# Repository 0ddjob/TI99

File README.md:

# [PSU Replacement](/TI994A_PSU_Replacement)
A fork of a fork.  <br>
Created a version using KiCad 9, with rounded corners and more information to make the build more "idiot proof".<br>

Replaces the 99/4A's original dual-voltage 18VAC/7.5VAC power supply with a regulated 12VDC supply.  The board then generates the required ±5VDC voltages using a DC-DC buck converter (+5VDC) and switching regulator (-5VDC).  The +12VDC comes directly from the external power supply.<br>

## Main Parts
- DFRobot DFR0831 DC-DC Buck Converter (+5VDC supply)
- Recom R-78CK5.0-0.5 Switching Regulator (-5VDC supply)
- Vishay SUP53P06-20 MOSFET (protects against reverse polarity DC input)
- G-Switch SS-22G88-G090 DPDT switch (need to trim a little)

## Original Designs
- [Johnny Blanchard's original](https://codeberg.org/Jonn-reenthused/TI99-4A-dc-power-board)
- [dabone's fork](https://github.com/dabonetn/ti99psu-replacement)

## Status
- 2-Nov-2025: Designed, not yet fabbed & tested, need to double-check switch position

# [Joystick Adaptor](/JoystickAdaptor)
Wanted to design my own joystick adaptor, so I did.

# [Cassette Adaptor #1](/CassetteAdaptor)
Wanted to design a cassette adaptor as an alternative to using a cable because, why not?  I normally play WAV files from my computer using a cable - this design lets me simply plug the cable into.<br>

This design is vertical and plugs into the DE9 socket to provide a 3.5mm EAR and 3.5mm MIC socket for CS1.<br>

# [Cassette Adaptor #2](/CassetteAdaptor2)
This design is horizontal and plugs into the DE9 socket to provide a 3.5mm EAR and 3.5mm MIC socket for CS1.<br>

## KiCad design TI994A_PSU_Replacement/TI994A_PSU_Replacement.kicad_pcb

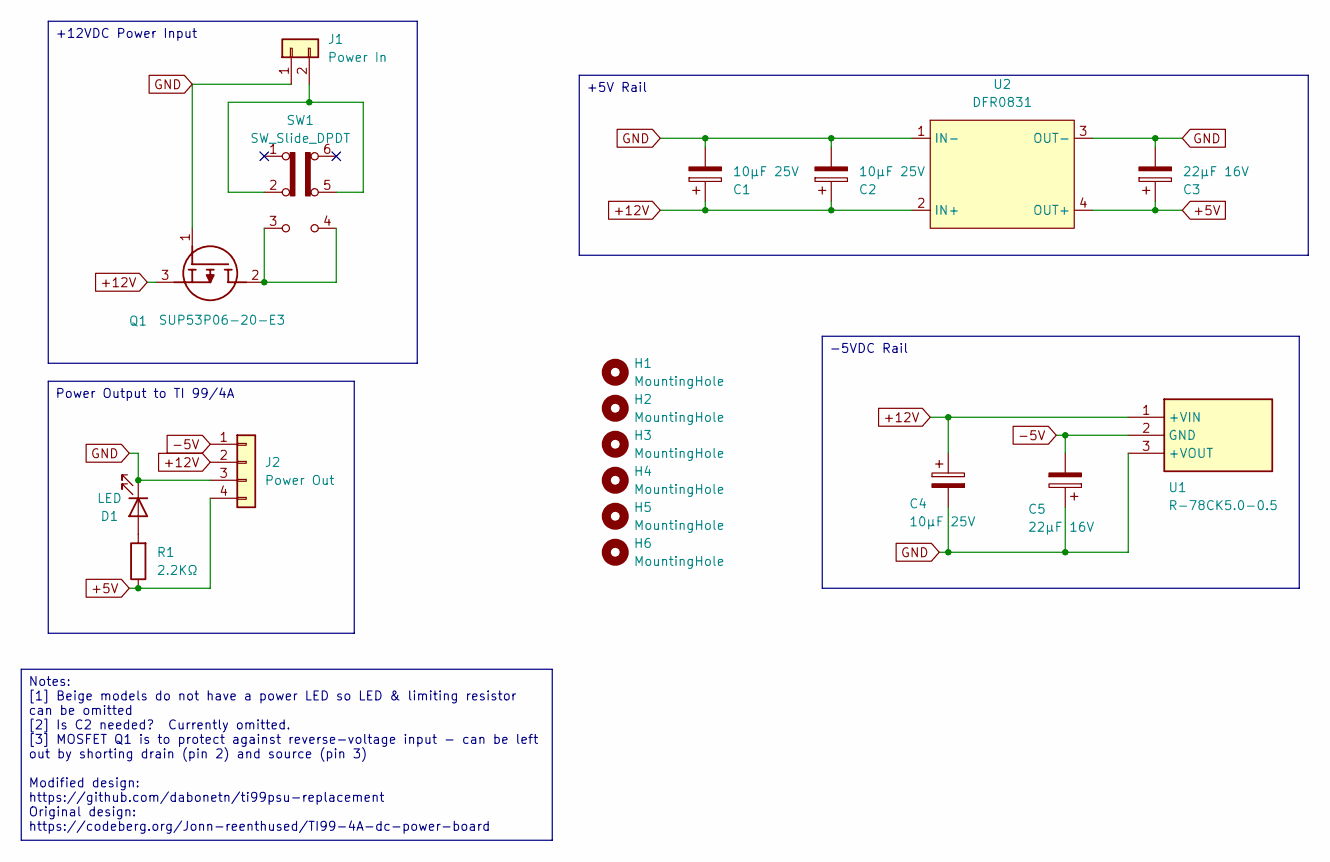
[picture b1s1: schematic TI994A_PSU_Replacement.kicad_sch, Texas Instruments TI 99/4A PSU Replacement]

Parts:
C1, C2, C4: 10µF 25V; C_Radial_D5.0mm_H5.0mm_P2.00mm
C3, C5: 22µF 16V; C_Radial_D5.0mm_H5.0mm_P2.00mm
D1: LED; LED_D5.0mm
H1, H2, H3, H4, H5: MountingHole; MountingHole_4mm
H6: MountingHole; MountingHole_6mm
J1: Power In; JST_VH_B2P-VH_1x02_P3.96mm_Vertical
J2: Power Out; JST_VH_B4P-VH_1x04_P3.96mm_Vertical
Q1: SUP53P06-20-E3; TO254P465X1028X1931-3P; Mouser Part Number 781-SUP53P06-20-E3
R1: 2.2KΩ; R_Axial_DIN0207_L6.3mm_D2.5mm_P7.62mm_Horizontal
SW1: SW_Slide_DPDT; SS-22G88-G090 DPDT
U1: R-78CK5.0-0.5; R78CK5005; Manufacturer_Part_Number R-78CK5.0-0.5
U2: DFR0831

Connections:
+5V: C3.1, J2.4, R1.1, U2.4 (OUT+)
+12V: C1.1, C2.1, C4.1, J2.2, Q1.3 (S), U1.1 (+VIN), U2.2 (IN+)
-5V: C5.2, J2.1, U1.2 (GND)
GND: C1.2, C2.2, C3.2, C4.2, C5.1, D1.1 (K), J1.1, J2.3, Q1.1 (G), U1.3 (+VOUT), U2.1 (IN-), U2.3 (OUT-)
unnamed: D1.2 (A), R1.2
unnamed: J1.2, SW1.2 (B), SW1.5 (B)
unnamed: Q1.2 (D), SW1.3 (C), SW1.4 (A)

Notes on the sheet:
+12VDC Power Input
-5VDC Rail
Power Output to TI 99/4A
Notes: [1] Beige models do not have a power LED so LED & limiting resistor can be omitted [2] Is C2 needed? Currently omitted. [3] MOSFET Q1 is to protect against reverse-voltage input - can be left out by shorting drain (pin 2) and source (pin 3) Modified design: https://github.com/dabonetn/ti99ps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
+5V Rail

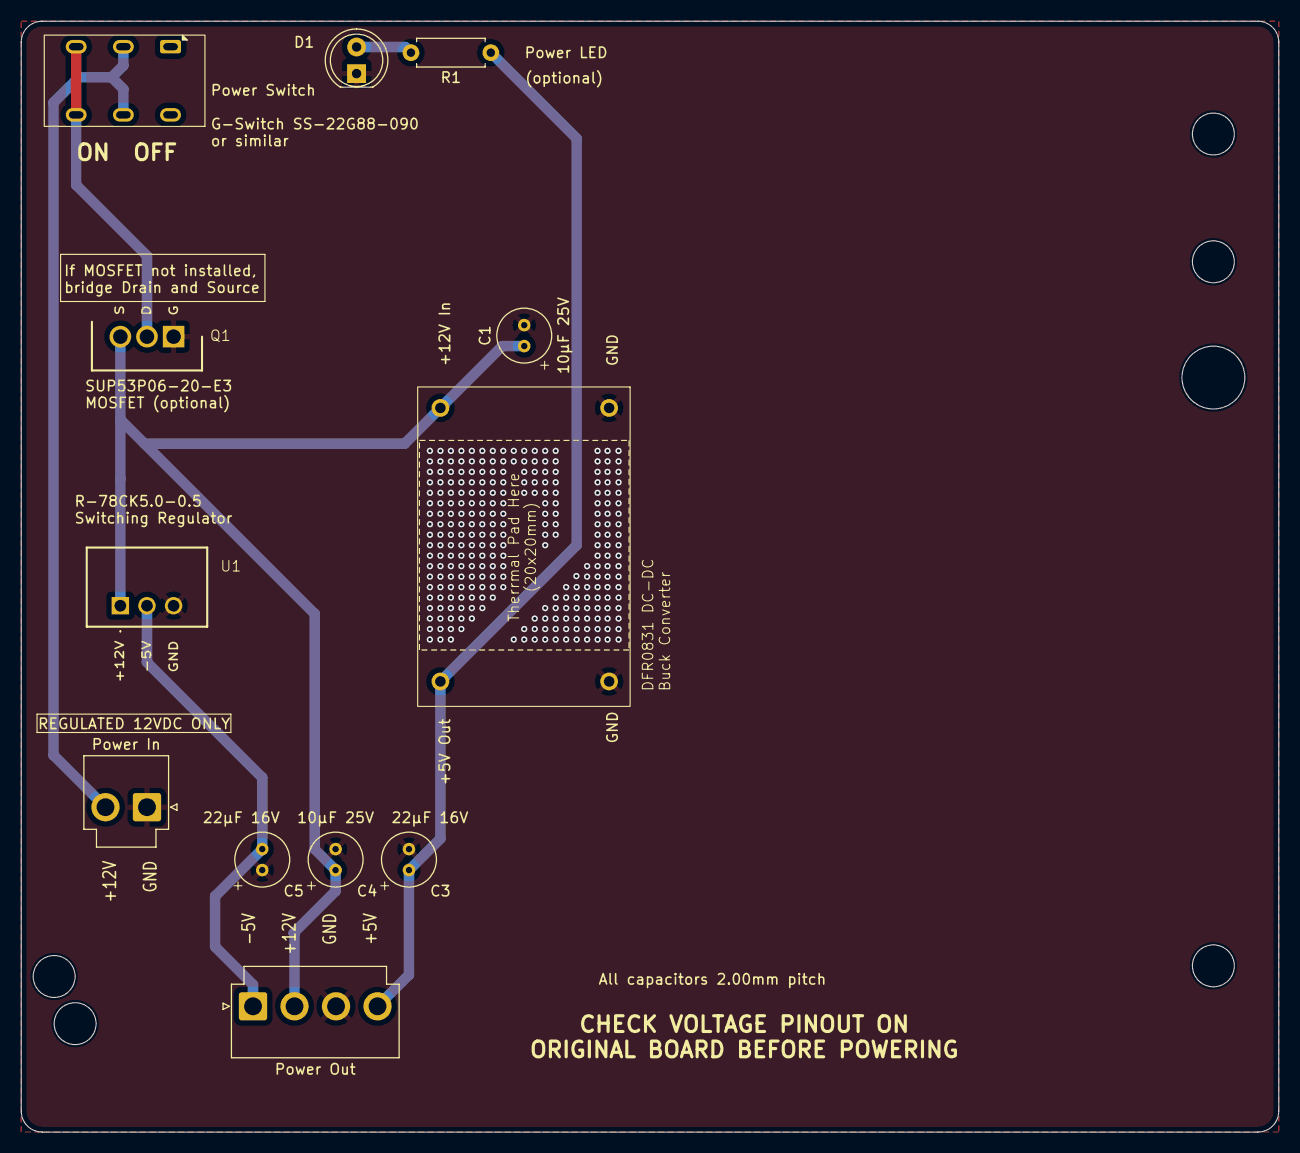
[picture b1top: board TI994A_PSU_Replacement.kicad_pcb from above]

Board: 2 copper layers, 120.0 x 106.0 mm, 18 parts (0 on the bottom side), 7 nets.

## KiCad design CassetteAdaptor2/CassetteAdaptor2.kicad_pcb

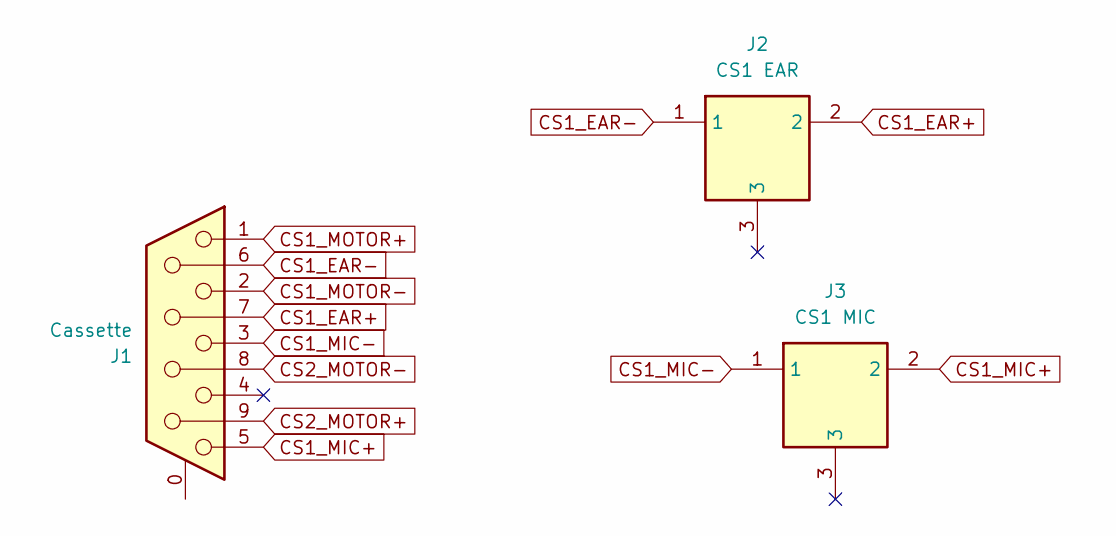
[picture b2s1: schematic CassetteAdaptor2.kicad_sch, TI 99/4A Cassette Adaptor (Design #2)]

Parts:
J1: Cassette; DSUB-9_Pins_EdgeMount_P2.77mm
J2: CS1 EAR; MJ3536N; Mouser Part Number 490-MJ-3536N
J3: CS1 MIC; MJ3536N; Mouser Part Number 490-MJ-3536N

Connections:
CS1_EAR+: J1.7, J2.2
CS1_EAR-: J1.6, J2.1
CS1_MIC+: J1.5, J3.2
CS1_MIC-: J1.3, J3.1
CS1_MOTOR+: J1.1
CS1_MOTOR-: J1.2
CS2_MOTOR+: J1.9
CS2_MOTOR-: J1.8

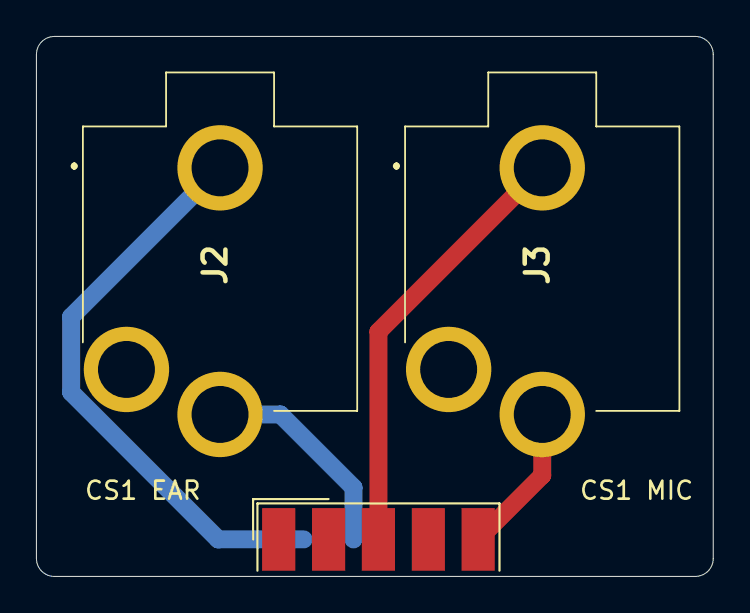
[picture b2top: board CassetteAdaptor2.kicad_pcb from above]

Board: 2 copper layers, 37.6 x 30.0 mm, 3 parts (0 on the bottom side), 4 nets.

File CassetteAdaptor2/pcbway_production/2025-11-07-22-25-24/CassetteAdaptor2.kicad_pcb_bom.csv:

Designator,Quantity,Value,Footprint,Package,MPN,DNP,Mount_Type,Description,Height,Mouser Part Number,Mouser Price/Stock,Manufacturer_Name
J1,1,Cassette,DSUB-9_Pins_EdgeMount_P2.77mm,,,,smt,"9-pin D-SUB connector, socket (female), Mounting Hole",,,,
J2,1,CS1 EAR,MJ3536N,,MJ-3536N,,tht,"3.5 mm, Mono, Right Angle, Through Hole, 2 Conductors, 1 Internal Switch, Audio Jack Connector",10,490-MJ-3536N,https://www.mouser.co.uk/ProductDetail/Same-Sky/MJ-3536N?qs=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,Same Sky
J3,1,CS1 MIC,MJ3536N,,MJ-3536N,,tht,"3.5 mm, Mono, Right Angle, Through Hole, 2 Conductors, 1 Internal Switch, Audio Jack Connector",10,490-MJ-3536N,https://www.mouser.co.uk/ProductDetail/Same-Sky/MJ-3536N?qs=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,Same Sky

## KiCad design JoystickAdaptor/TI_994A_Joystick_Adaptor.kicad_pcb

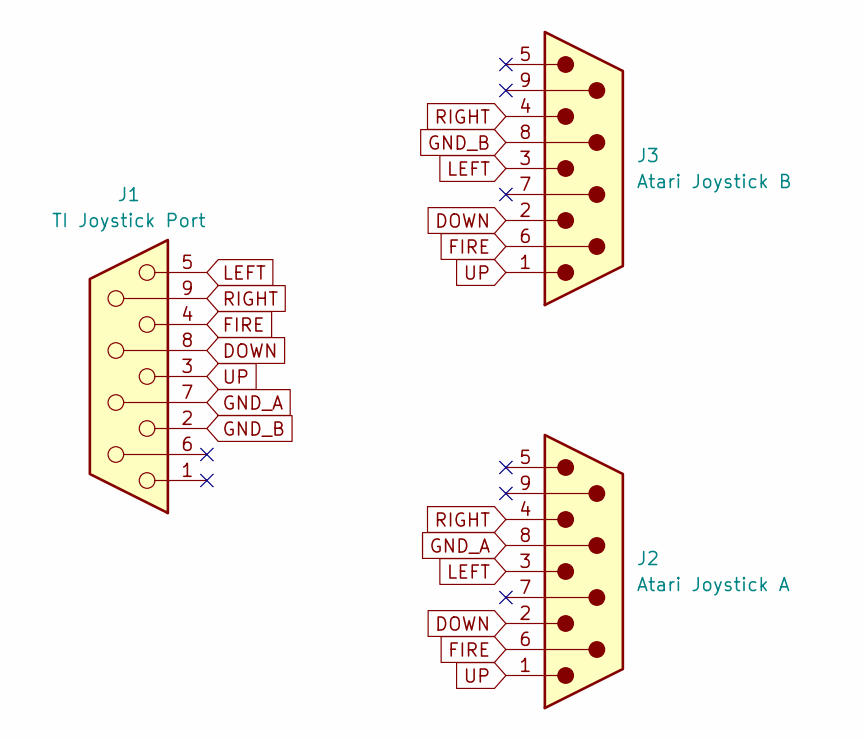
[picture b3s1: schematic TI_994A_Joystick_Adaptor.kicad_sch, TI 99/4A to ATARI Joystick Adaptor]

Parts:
J1: TI Joystick Port; DSUB-9_Socket_Vertical_P2.77x2.84mm
J2: Atari Joystick A; DSUB-9_Pins_Vertical_P2.77x2.84mm
J3: Atari Joystick B; DSUB-9_Pins_Vertical_P2.77x2.84mm

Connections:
DOWN: J1.8, J2.2, J3.2
FIRE: J1.4, J2.6, J3.6
GND_A: J1.7, J2.8
GND_B: J1.2, J3.8
LEFT: J1.5, J2.3, J3.3
RIGHT: J1.9, J2.4, J3.4
UP: J1.3, J2.1, J3.1

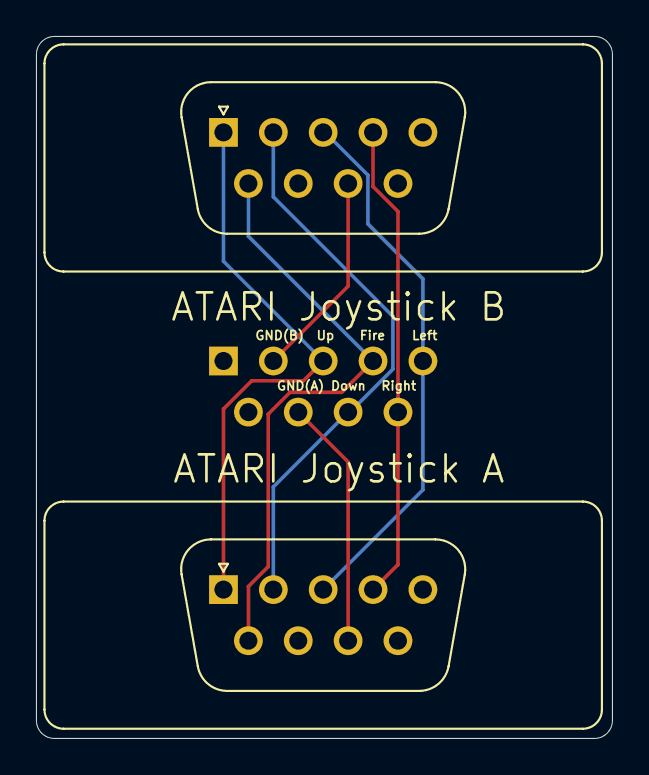
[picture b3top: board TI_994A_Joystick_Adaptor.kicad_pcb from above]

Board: 2 copper layers, 32.0 x 39.0 mm, 3 parts (1 on the bottom side), 7 nets.

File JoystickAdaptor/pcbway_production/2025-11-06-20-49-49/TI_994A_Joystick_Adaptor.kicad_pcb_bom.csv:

Designator,Quantity,Value,Footprint,Package,MPN,DNP,Mount_Type,Description
J1,1,TI Joystick Port,DSUB-9_Socket_Vertical_P2.77x2.84mm,,,,tht,"9-pin D-SUB connector, socket (female)"
J2,1,Atari Joystick A,DSUB-9_Pins_Vertical_P2.77x2.84mm,,,,tht,"9-pin D-SUB connector, pins (male)"
J3,1,Atari Joystick B,DSUB-9_Pins_Vertical_P2.77x2.84mm,,,,tht,"9-pin D-SUB connector, pins (male)"

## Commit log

2025-11-01 Added BOM
2025-11-01 Added 3D preview
2025-11-01 Added vias for better thermal distrubution
    Thanks to tip from Mr Waalkman
2025-11-01 PCB text improvements
2025-11-06 Initial commit of joystick converter
2025-11-07 Added missing +12V track
2025-11-07 Initial commit of 2nd design
2025-11-11 PCB text changes
